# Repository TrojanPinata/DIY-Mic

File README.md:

# DIY-Mic
A DIY microphone built using the design of DIY Perks and modified by me. I wanted a decent mic and I didn’t want to spend the money on one, so when I saw this video it seemed like the perfect opportunity for me to both have fun with a electronics project and get a decent mic.

# Credit
This would not be possible without DIY Perks and the resources he provided. The stripboard and base wiring diagram are extremely helpful as well as his overall attention to detail. Video link here: https://www.youtube.com/watch?app=desktop&v=LoQu3XXIayc

# PCB Assembly Note
If you are building the PCB version of this project, please note that you should reverse the polarity of capacitor C2 (the bottom most capacitor on the board) as it should have a negative voltage coming from the regulator. (2026-03-31)

# Acquiring Parts
For this build, there are a number of parts you will need. In the video he goes all out in brass, which for most of us at home, seems absurd because of how uncommon it is to have the exact diameter of brass tubing or brass mesh lying around. I ran into this problem early on, so I designed a box and lid for mine that should work in place of a ton of brass and wood and is easily 3d printable (STLs above). I know most people don't have 3d printers, but I feel like this is slightly more accessible for those without hordes of tools. I also used a mic arm I found in the trash to make the arm instead of building it. So, with the 'housing' out of the way, everything else can be found in this list (or at least what I used/needed):

https://docs.google.com/spreadsheets/d/1pQlkRerO5geoDNLEWXTUVbyJalM7nESn/edit#gid=497893649

As you can probably tell, the pricing is pretty high compared to the sticker price. That was the number I was able to get it down to after some alternatives (and using the wrong materials and finding out they don’t work. The electronics can either be found on alibaba or ebay, I chose ebay because that was the only way I could finish this in less then 2 months. With all of that, I nicked a old audio cable, a old rc car motor, and some resistors in order to start building.

# Actually Building the Thing
The first thing I did (and this pretty much goes with the order the parts arrived to me) was the preamp box. I put some brass mesh on the bottom and glued the template on some protoboard, soldered all of the parts on and drilled corner holes. In hindsight, the pegs I included were pretty useless (and off center) so they should probably just be removed. I layered some tape over the bottom mesh to prevent shorts and plopped the whole thin in. I then added the potentiometer to the lid. Note, I live in the US, so I was unable to get a THAT1512, and I had to go with an INA217. This isn't really a problem, just know that on my final build, I attached a 2.2kOhm resistor to the potentiometer because of how the gain settings work. I assume there may be some overall gain differences, but we'll get to that in the review section. I pretty much did that and threw in the ADC (Analog Digital Converter) with some tape covering it. I ordered a pretty cheap one, but it has a led and I kind of like that because of how much easier it made troubleshooting. All of these parts can be connected to the main board and the ADC can be connected to the USB-C breakout board. Power wires can be connected and that should be everything that is directly connected.

Partially Assembled:

Some notes real quick before putting anything on the board:

The two capacitors on the right need to be flipped 180 degrees so the polarities are swapped, and all of the rest are fine, with the white being positive and dark being negative. Other than that, you can build it however you want. I found that its better to use a little bit thicker audio cable, because the stuff that i used was really thin and I ended up having to solder it a bit to get the connectors to stay on.

And on that note lets talk about the cables. So yes, you can use solder removing copper strips like he did. But I had extremely bad luck with mine all just being flat to begin with, and thus not folding back into a tube. So as a result, I just ordered some proper sheathing. Honestly, worth it. I ended up threading the enameled wires through much easier than I thought it would be. So, with those two out of the way, IU soldered them together and used a heatshrink for the binding. Now, I just want to note that the way DIY Perks sands the enamel off of those thin wires is correct, however, be extremely careful because if you go too far, they are super easy to short (trust me I know from experience). So, with that, you can plug the cable into the preamp and work on the mic. 

The mic, from my experience, has the parts that take the longest to get here. First of all, if you can get a JLI mic module, be my guest, but they seem to be always out of stock. I ordered mine from another place for a significant markup and I'm not even mad. At least it’s here. The transistors took a hot minute to get here (they were the last thing I needed, and I actually moved on to another project I got so sick of waiting on them. Once they did arrive though, its pretty much exactly as he said. However, I should note my module housing is also 3d printed and the grills are shaped using 3d printed parts. Crushed the mesh in between the mold and formed the grills, soldered them with the transistor mic combo like a sandwich, and jammed it into the housing. I added all of those holes for maximum sound quality, and it seems to work. I will note that you should probably put something between the grill and transistor, as well as between the legs due to possible shorting, as that is what caused a lot of my early trouble. With that, that’s basically everything. I used some tape to secure the lid onto the box and hot glue to keep some loose things secured and it just kind of works. 

The rear of the module is really jank for me. Don't do this lol:

# Review
Overall its a good mic. I've been using it for the past few weeks and everyone who’s seen it really likes it. It's kind of scuffed but sounds fantastic (most of the time). I should note that I had a insane amount of gain until I added a resistor between the potentiometer. I still do, and I probably just need more shielding, but it sounds fine over discord and for personal use so I don't mind too much. I'll fix it when I need it. 

The big things about this project I would note for anyone looking to do this is that a.) it costs more then you expect, b.) it's not going to look anything like the video, and c.) there will be more noise then you think there will be. Other then that, happy building!

# Edit - 02/11/2022
Hello, I thought I was done with this project but let me tell you I've got a update that may interest you. Back when I was picking out the parts for this, I chose to use a INA217 because it was available and the only way for me to get a THAT1512 was a long 4 month wait from the UK. So, I bought the THAT1512 and the INA217 and hoped it would work out. I used the INA217 for the past few months and I can say its definitely good. Not great, not bad, just good. And I was happy with that. I had to use a higher resistance resistor in place of the potentiometer but overall, I didn't really mind it. There was a little bit of background noise at some frequencies, but I just thought that was my bad shielding.

I just got my THAT1512, slapped that bad boy in there and let me tell you, it's a whole world of difference. The two chips should be very electrically similar according to their data sheets, with only a little bit of gain differences, but the difference is insane. No more noise went back to the potentiometer, better volume (even at the same levels), and overall, a better time. Anyway, hope that interests you. They're kind of hard to find so if you can get one then do. Otherwise INA217 is still pretty good.

# Update - 10/05/2023
Hello! It has been a while. I never thought I'd update this repository again, but I just wanted to stop in after a while and clean up by bringing some modifications to the original project and overall design. I found the original mic design to be pretty cool, but horribly inconvenient to use. I ended up switching to another microphone for a while, but I thought I'd come back with some real quality of life changes to make this actually usable for me. The main things I changed were swapping the housing for a BM-800 microphone body (one of the worst sounding mics on the market - but cheap to fit with the theme) and designing a PCB which follows the original stripboard. My PCBs totaled a cool five dollars, and the quality of the entire thing is significantly higher. 

The end result was much better than the original, with significantly less noise and much more versatility. I added the KiCad files to the repo but don’t expect too much. I found the mic gets a bit hotter and has a much lower gain setting (100 ohms) due to the lower noise but is overall pretty good – especially when compared to the original. These upgrades make this 99% more usable for me and hopefully if you either still use this project or something similar this update is helpful.

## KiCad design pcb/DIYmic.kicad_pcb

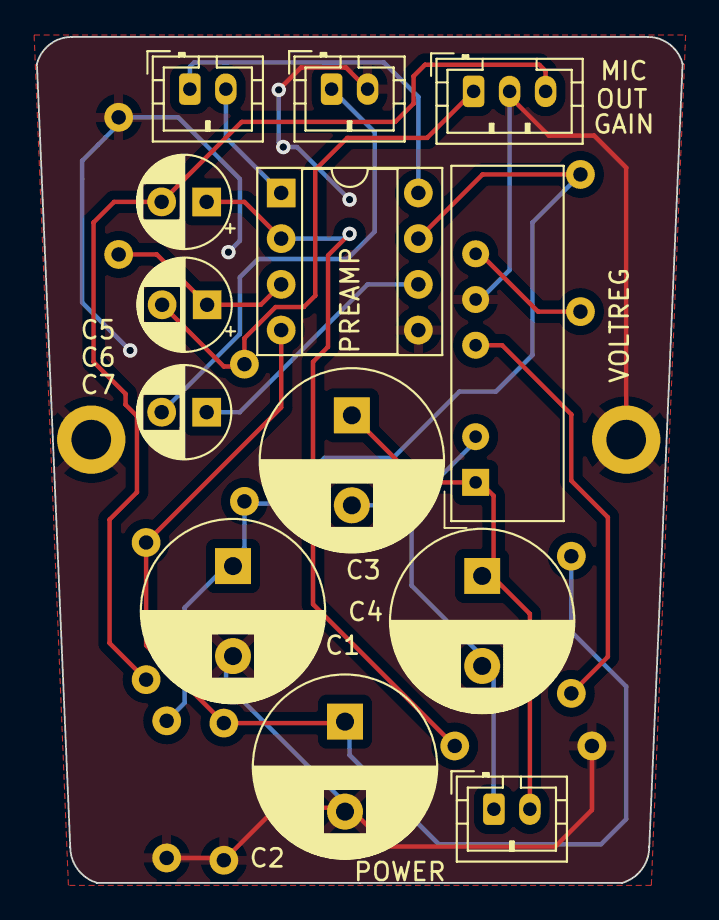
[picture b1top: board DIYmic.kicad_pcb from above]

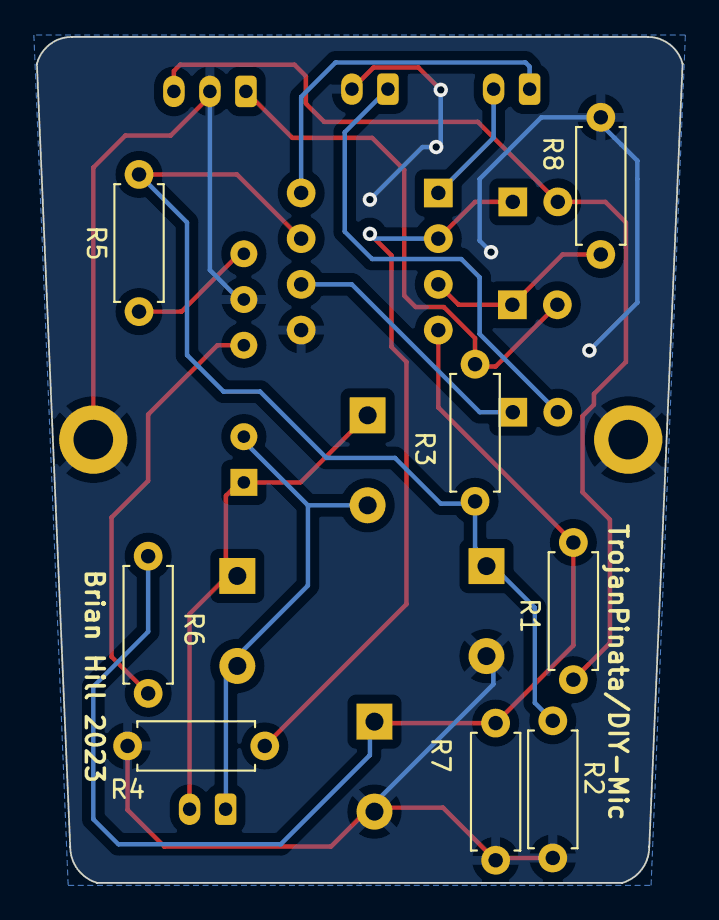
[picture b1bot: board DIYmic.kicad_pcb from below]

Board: 2 copper layers, 35.9 x 47.0 mm, 21 parts (8 on the bottom side), 15 nets.

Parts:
C1, C2, C3, C4: 2200uF; CP_Radial_D10.0mm_P5.00mm
C5, C6, C7: 22uF; CP_Radial_D5.0mm_P2.50mm
GAIN: Conn_01x02_Socket; JST_PH_B2B-PH-K_1x02_P2.00mm_Vertical
MIC: Conn_01x03_Socket; JST_PH_B3B-PH-K_1x03_P2.00mm_Vertical
OUT: Conn_01x02_Socket; JST_PH_B2B-PH-K_1x02_P2.00mm_Vertical
POWER: Conn_01x02_Socket; JST_PH_B2B-PH-K_1x02_P2.00mm_Vertical
PREAMP: THAT1512; DIP-8_W7.62mm_Socket
R1, R2, R3, R7: 2.2k; R_Axial_DIN0207_L6.3mm_D2.5mm_P7.62mm_Horizontal
R4, R8: 3.9k; R_Axial_DIN0207_L6.3mm_D2.5mm_P7.62mm_Horizontal
R5, R6: 100; R_Axial_DIN0207_L6.3mm_D2.5mm_P7.62mm_Horizontal
VOLTREG: NMA0515SC; Converter_DCDC_Murata_NMAxxxxSC_THT

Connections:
unnamed: GAIN.1, PREAMP.8
unnamed: GAIN.2, PREAMP.1
unnamed: C5.2, MIC.1, R3.2
unnamed: C1.2, C2.2, MIC.2, OUT.2, PREAMP.5, R2.2, R4.2, R7.2, R8.2, VOLTREG.5 (0V)
unnamed: C6.2, MIC.3, R1.2
unnamed: C7.2, OUT.1
unnamed: C3.2, C4.2, POWER.1, VOLTREG.2 (VIN-)
unnamed: C3.1, C4.1, POWER.2, VOLTREG.1 (VIN+)
unnamed: C6.1, PREAMP.2, R4.1
unnamed: C5.1, PREAMP.3, R8.1
unnamed: C2.1, PREAMP.4, R1.1, R6.2, R7.1
unnamed: C7.1, PREAMP.6
unnamed: C1.1, PREAMP.7, R2.1, R3.1, R5.2
unnamed: R5.1, VOLTREG.6 (VOUT+)
unnamed: R6.1, VOLTREG.4 (VOUT-)

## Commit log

2021-11-30 Added pics
2021-11-30 write up
2021-11-30 sized
2021-11-30 Finished ig
2021-11-30 updated pics
2022-01-07 Updated Stripboard
    As per requests, stripboard now has its polarity flipped to what it should be. No more relying on text. White positive, grey negative. Nothing else changed.
2022-02-12 Edit 02/11/2022
2023-02-08 quick fix
    i am bad at spelling
2023-02-28 wow i am a bad typer
    always proof read your works kids
2023-10-05 feature update - quality of life and clean up
2026-03-31 Capacitor C2 Note
